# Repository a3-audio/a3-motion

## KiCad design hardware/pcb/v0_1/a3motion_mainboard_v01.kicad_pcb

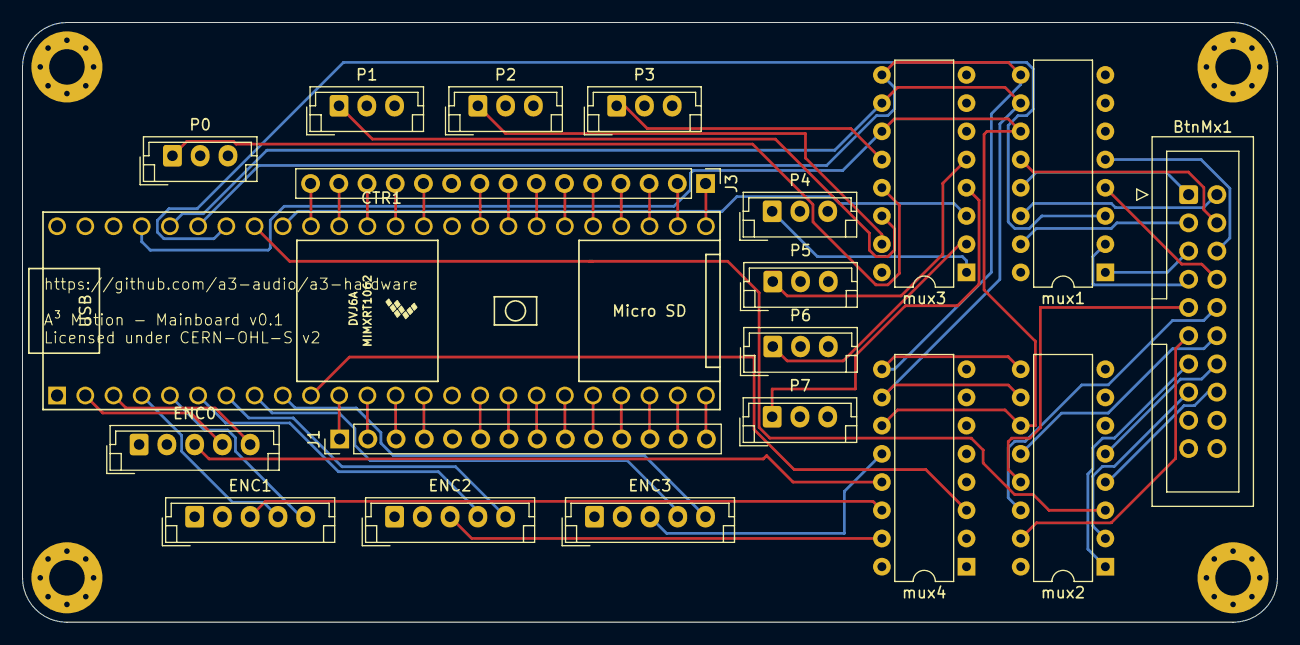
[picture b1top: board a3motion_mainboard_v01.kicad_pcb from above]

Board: 4 copper layers, 113.0 x 54.0 mm, 20 parts (0 on the bottom side), 72 nets.

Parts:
BtnMx1: Conn_02x09_Counter_Clockwise; IDC-Header_2x10_P2.54mm_Vertical
CTR1: Teensy4.1; Teensy41_my
ENC0, ENC1, ENC2, ENC3: Conn_01x05; JST_EH_B5B-EH-A_1x05_P2.50mm_Vertical
J1: Conn_01x14_Male; PinHeader_1x14_P2.54mm_Vertical
J3: Conn_01x15_Male; PinHeader_1x15_P2.54mm_Vertical
P0, P1, P2, P3, P4, P5, P6, P7: Conn_01x03; JST_EH_B3B-EH-A_1x03_P2.50mm_Vertical
mux1, mux2, mux3, mux4: 74HC4051; DIP-16_W7.62mm

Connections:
+3V3: BtnMx1.20, CTR1.15, CTR1.46, ENC0.2, ENC1.2, ENC2.2, ENC3.2, J1.5, P0.3, P1.3, P2.3, P3.3, P4.3, P5.3, P6.3, P7.3, mux1.16, mux2.16, mux3.16, mux4.16
GND: BtnMx1.19, CTR1.1, CTR1.34, CTR1.47, ENC0.1, ENC1.1, ENC2.1, ENC3.1, J3.10, P0.2, P1.2, P2.2, P3.2, P4.2, P5.2, P6.2, P7.2, mux1.6, mux1.7, mux1.8, mux2.6, mux2.7, mux2.8, mux3.6, mux3.7, mux3.8, mux4.6, mux4.7, mux4.8
unnamed: BtnMx1.1, mux1.13
unnamed: BtnMx1.2, mux1.14
unnamed: BtnMx1.3, mux1.15
unnamed: BtnMx1.4, mux1.12
unnamed: BtnMx1.5, mux1.1
unnamed: BtnMx1.6, mux1.5
unnamed: BtnMx1.7, mux1.2
unnamed: BtnMx1.8, mux1.4
unnamed: BtnMx1.9, mux2.13
unnamed: BtnMx1.10, mux2.14
unnamed: BtnMx1.11, mux2.15
unnamed: BtnMx1.12, mux2.12
unnamed: BtnMx1.13, mux2.1
unnamed: BtnMx1.14, mux2.5
unnamed: BtnMx1.15, mux2.2
unnamed: BtnMx1.16, mux2.4
unnamed: CTR1.11, J1.1
unnamed: CTR1.12, J1.2
unnamed: CTR1.13, J1.3
unnamed: CTR1.14, J1.4
unnamed: CTR1.16, J1.6
unnamed: CTR1.17, J1.7
unnamed: CTR1.18, J1.8
unnamed: CTR1.19, J1.9
unnamed: CTR1.20, J1.10
unnamed: CTR1.21, J1.11
unnamed: CTR1.22, J1.12
unnamed: CTR1.23, J1.13
unnamed: CTR1.24, J1.14
unnamed: CTR1.25, J3.1
unnamed: CTR1.26, J3.2
unnamed: CTR1.27, J3.3
unnamed: CTR1.28, J3.4
unnamed: CTR1.29, J3.5
unnamed: CTR1.30, J3.6
unnamed: CTR1.31, J3.7
unnamed: CTR1.32, J3.8
unnamed: CTR1.33, J3.9
unnamed: CTR1.35, J3.11
unnamed: CTR1.36, J3.12
unnamed: CTR1.37, J3.13
unnamed: CTR1.38, J3.14
unnamed: CTR1.39, J3.15
unnamed: ENC0.3, mux4.13
unnamed: ENC1.3, mux4.14
unnamed: ENC2.3, mux4.15
unnamed: ENC3.3, mux4.12
unnamed: P0.1, mux3.13
unnamed: P1.1, mux3.14
unnamed: P2.1, mux3.15
unnamed: P3.1, mux3.12
unnamed: P4.1, mux3.1
unnamed: P5.1, mux3.5
unnamed: P6.1, mux3.2
unnamed: P7.1, mux3.4
mux_btnMx1: CTR1.42, mux1.3
mux_btnMx2: CTR1.41, mux2.3
mux_btn_rEnc: CTR1.10, mux4.3
mux_porty: CTR1.40, mux3.3
rEnc0_CLK: CTR1.3, ENC0.5
rEnc0_DT: CTR1.2, ENC0.4
rEnc1_CLK: CTR1.5, ENC1.5
rEnc1_DT: CTR1.4, ENC1.4
rEnc2_CLK: CTR1.7, ENC2.5
rEnc2_DT: CTR1.6, ENC2.4
rEnc3_CLK: CTR1.9, ENC3.5
rEnc3_DT: CTR1.8, ENC3.4
s0: CTR1.45, mux1.11, mux2.11, mux3.11, mux4.11
s1: CTR1.44, mux1.10, mux2.10, mux3.10, mux4.10
s2: CTR1.43, mux1.9, mux2.9, mux3.9, mux4.9

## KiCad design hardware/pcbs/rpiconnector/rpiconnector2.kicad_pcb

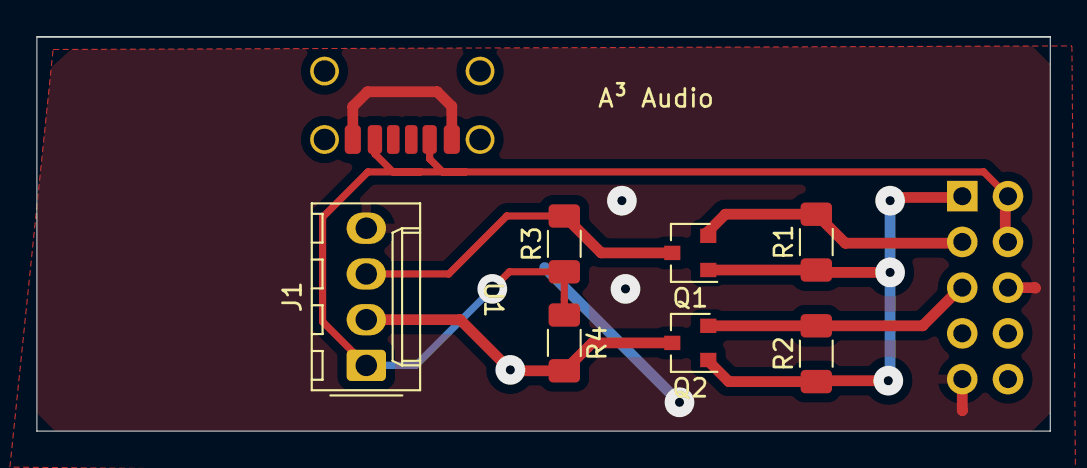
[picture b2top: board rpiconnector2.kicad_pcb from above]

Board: 2 copper layers, 56.3 x 21.9 mm, 9 parts (1 on the bottom side), 7 nets.

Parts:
J1: molex1x04; Molex_KK-254_AE-6410-04A_1x04_P2.54mm_Vertical
J2: Conn_02x05_Odd_Even; PinSocket_2x05_P2.54mm_Vertical
Q1, Q2: BSS138
R1, R2, R3, R4: 10k; R_1206_3216Metric_Pad1.30x1.75mm_HandSolder
U1: USB-C

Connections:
3v3: J2.1, Q1.1 (G), Q2.1 (G), R1.1, R2.1
5v: J1.1, J2.2, J2.4, R3.1, R4.1, U1.2 (VBUS), U1.5 (VBUS)
GND: J1.4, J2.6, J2.9, U1.1 (GND), U1.6 (GND)
SCL: J2.5, Q2.2 (S), R2.2
SCL_5V: J1.2, Q2.3 (D), R4.2
SDA: J2.3, Q1.2 (S), R1.2
SDA_5v: J1.3, Q1.3 (D), R3.2

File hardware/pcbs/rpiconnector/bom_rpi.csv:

"Reference","Value","Datasheet","Footprint","Qty","DNP"
"J1","molex1x04","~","Connector_Molex:Molex_KK-254_AE-6410-04A_1x04_P2.54mm_Vertical","1",""
"J2","Conn_02x10_Odd_Even","~","Connector_PinSocket_2.54mm:PinSocket_2x10_P2.54mm_Vertical","1",""
"Q1,Q2","BSS138","https://www.onsemi.com/pub/Collateral/BSS138-D.PDF","3dAudioFoot:BSS138","2",""
"R1,R2,R3,R4","10k","~","Resistor_SMD:R_1206_3216Metric_Pad1.30x1.75mm_HandSolder","4",""
"U1","USB-C","","3dAudioFoot:USB-C","1",""

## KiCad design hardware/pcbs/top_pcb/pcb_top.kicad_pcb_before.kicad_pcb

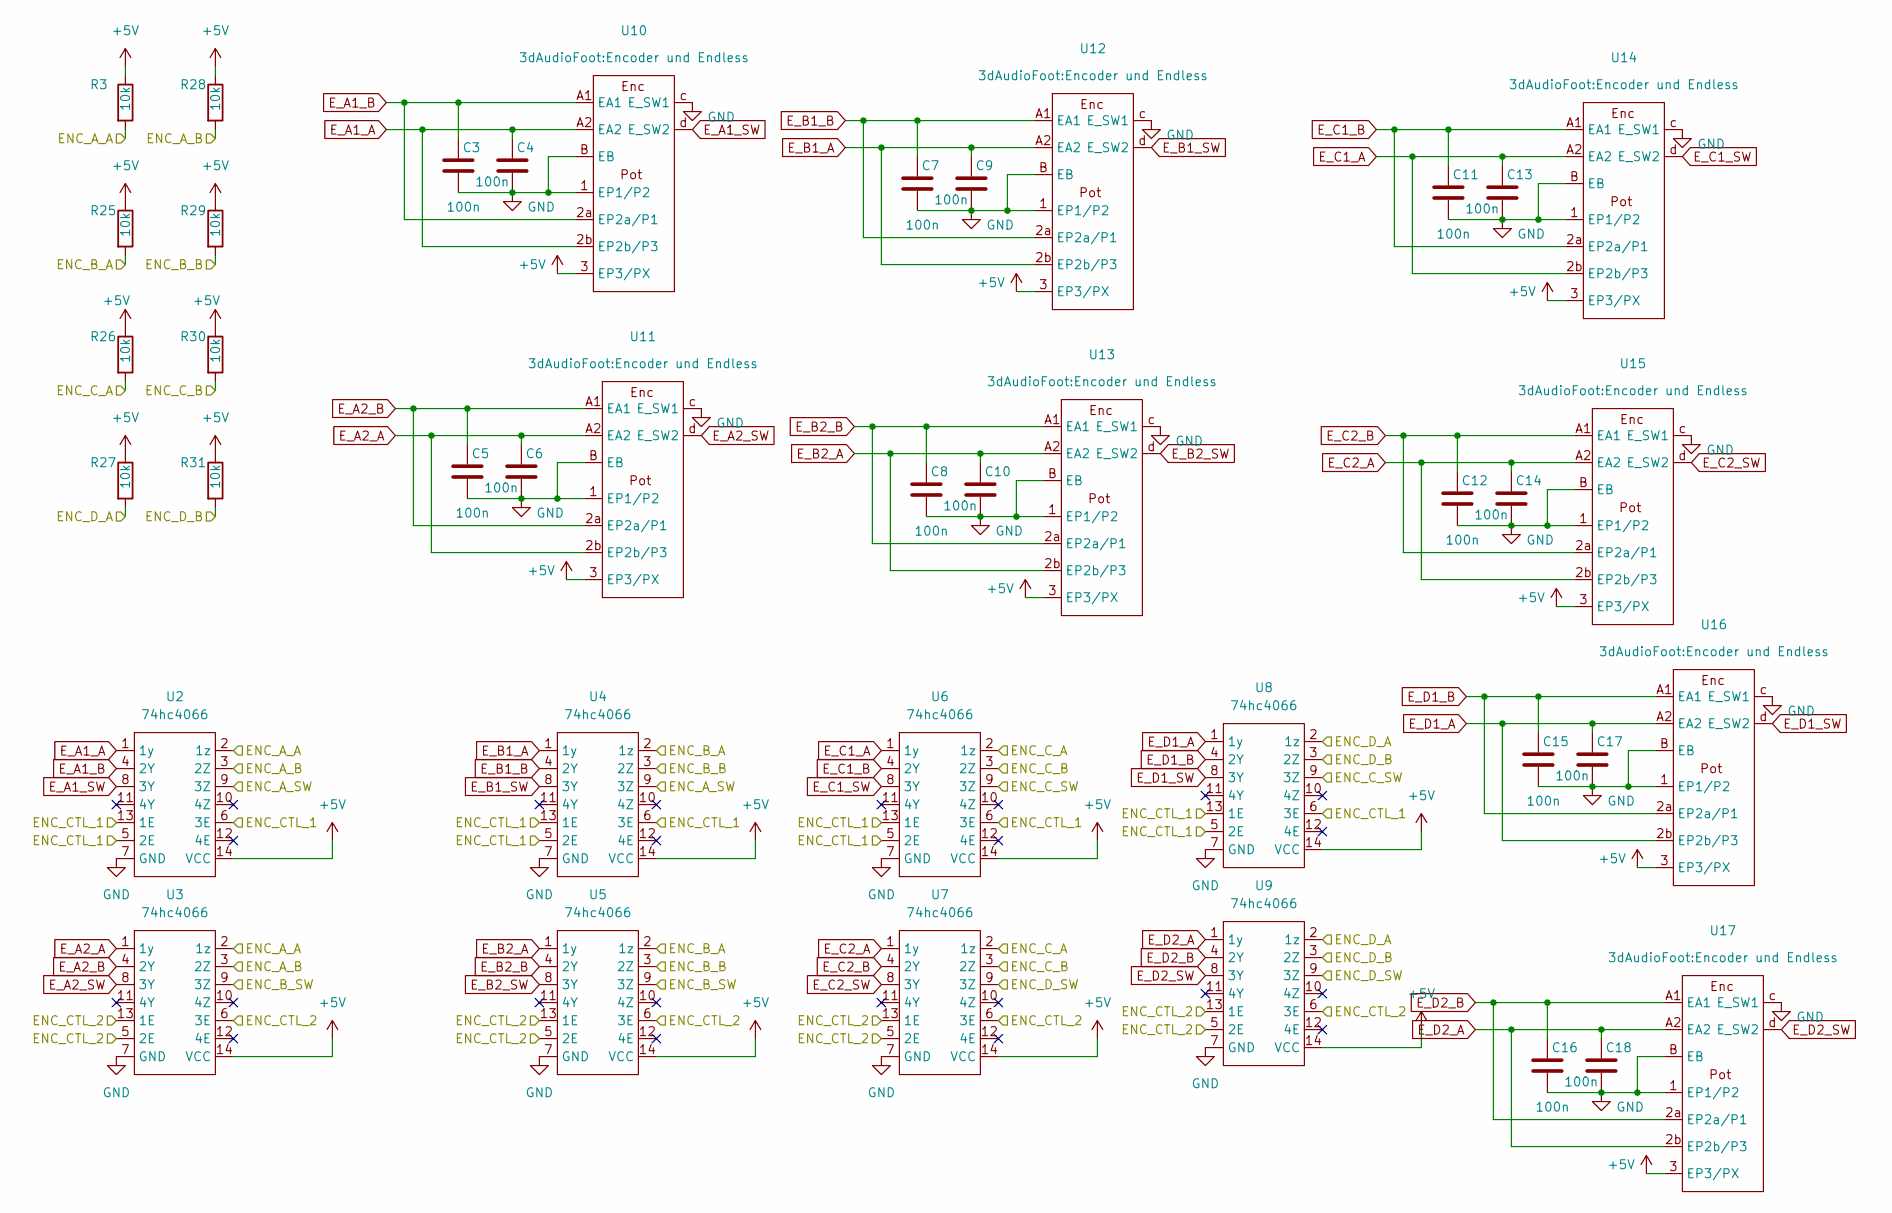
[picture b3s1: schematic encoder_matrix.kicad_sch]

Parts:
C3, C4, C5, C6, C7, C8, C9, C10, C11, C12, C13, C14, C15, C16, C17, C18: 100n; C_1206_3216Metric_Pad1.33x1.80mm_HandSolder
R3, R25, R26, R27, R28, R29, R30, R31: 10k; R_1206_3216Metric_Pad1.30x1.75mm_HandSolder
U2, U3, U4, U5, U6, U7, U8, U9: 74hc4066; SOIC-14_3.9x8.7mm_P1.27mm
U10, U11, U12, U13, U14, U15, U16, U17: Encoder und Endless

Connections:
+5V: R3.1, R25.1, R26.1, R27.1, R28.1, R29.1, R30.1, R31.1, U2.14 (VCC), U3.14 (VCC), U4.14 (VCC), U5.14 (VCC), U6.14 (VCC), U7.14 (VCC), U8.14 (VCC), U9.14 (VCC), U10.3 (EP3/PX), U11.3 (EP3/PX), U12.3 (EP3/PX), U13.3 (EP3/PX), U14.3 (EP3/PX), U15.3 (EP3/PX), U16.3 (EP3/PX), U17.3 (EP3/PX); also elsewhere on the board
/Untitled Sheet/ENC_A_A: R3.2, U2.2 (1z), U3.2 (1z); also elsewhere on the board
/Untitled Sheet/ENC_A_B: R28.2, U2.3 (2Z), U3.3 (2Z); also elsewhere on the board
/Untitled Sheet/ENC_A_SW: U2.9 (3Z), U4.9 (3Z); also elsewhere on the board
/Untitled Sheet/ENC_B_A: R25.2, U4.2 (1z), U5.2 (1z); also elsewhere on the board
/Untitled Sheet/ENC_B_B: R29.2, U4.3 (2Z), U5.3 (2Z); also elsewhere on the board
/Untitled Sheet/ENC_B_SW: U3.9 (3Z), U5.9 (3Z); also elsewhere on the board
/Untitled Sheet/ENC_CTL_1: U2.5 (2E), U2.6 (3E), U2.13 (1E), U4.5 (2E), U4.6 (3E), U4.13 (1E), U6.5 (2E), U6.6 (3E), U6.13 (1E), U8.5 (2E), U8.6 (3E), U8.13 (1E); also elsewhere on the board
/Untitled Sheet/ENC_CTL_2: U3.5 (2E), U3.6 (3E), U3.13 (1E), U5.5 (2E), U5.6 (3E), U5.13 (1E), U7.5 (2E), U7.6 (3E), U7.13 (1E), U9.5 (2E), U9.6 (3E), U9.13 (1E); also elsewhere on the board
/Untitled Sheet/ENC_C_A: R26.2, U6.2 (1z), U7.2 (1z); also elsewhere on the board
/Untitled Sheet/ENC_C_B: R30.2, U6.3 (2Z), U7.3 (2Z); also elsewhere on the board
/Untitled Sheet/ENC_C_SW: U6.9 (3Z), U8.9 (3Z); also elsewhere on the board
/Untitled Sheet/ENC_D_A: R27.2, U8.2 (1z), U9.2 (1z); also elsewhere on the board
/Untitled Sheet/ENC_D_B: R31.2, U8.3 (2Z), U9.3 (2Z); also elsewhere on the board
/Untitled Sheet/ENC_D_SW: U7.9 (3Z), U9.9 (3Z); also elsewhere on the board
E_A1_A: C4.1, U2.1 (1y), U10.2b (EP2b/P3), U10.A2 (EA2)
E_A1_B: C3.1, U2.4 (2Y), U10.2a (EP2a/P1), U10.A1 (EA1)
E_A1_SW: U2.8 (3Y), U10.d (E_SW2)
E_A2_A: C6.1, U3.1 (1y), U11.2b (EP2b/P3), U11.A2 (EA2)
E_A2_B: C5.1, U3.4 (2Y), U11.2a (EP2a/P1), U11.A1 (EA1)
E_A2_SW: U3.8 (3Y), U11.d (E_SW2)
E_B1_A: C9.1, U4.1 (1y), U12.2b (EP2b/P3), U12.A2 (EA2)
E_B1_B: C7.1, U4.4 (2Y), U12.2a (EP2a/P1), U12.A1 (EA1)
E_B1_SW: U4.8 (3Y), U12.d (E_SW2)
E_B2_A: C10.1, U5.1 (1y), U13.2b (EP2b/P3), U13.A2 (EA2)
E_B2_B: C8.1, U5.4 (2Y), U13.2a (EP2a/P1), U13.A1 (EA1)
E_B2_SW: U5.8 (3Y), U13.d (E_SW2)
E_C1_A: C13.1, U6.1 (1y), U14.2b (EP2b/P3), U14.A2 (EA2)
E_C1_B: C11.1, U6.4 (2Y), U14.2a (EP2a/P1), U14.A1 (EA1)
E_C1_SW: U6.8 (3Y), U14.d (E_SW2)
E_C2_A: C14.1, U7.1 (1y), U15.2b (EP2b/P3), U15.A2 (EA2)
E_C2_B: C12.1, U7.4 (2Y), U15.2a (EP2a/P1), U15.A1 (EA1)
E_C2_SW: U7.8 (3Y), U15.d (E_SW2)
E_D1_A: C17.1, U8.1 (1y), U16.2b (EP2b/P3), U16.A2 (EA2)
E_D1_B: C15.1, U8.4 (2Y), U16.2a (EP2a/P1), U16.A1 (EA1)
E_D1_SW: U8.8 (3Y), U16.d (E_SW2)
E_D2_A: C18.1, U9.1 (1y), U17.2b (EP2b/P3), U17.A2 (EA2)
E_D2_B: C16.1, U9.4 (2Y), U17.2a (EP2a/P1), U17.A1 (EA1)
E_D2_SW: U9.8 (3Y), U17.d (E_SW2)
GND: C3.2, C4.2, C5.2, C6.2, C7.2, C8.2, C9.2, C10.2, C11.2, C12.2, C13.2, C14.2, C15.2, C16.2, C17.2, C18.2, U2.7 (GND), U3.7 (GND), U4.7 (GND), U5.7 (GND), U6.7 (GND), U7.7 (GND), U8.7 (GND), U9.7 (GND), U10.1 (EP1/P2), U10.B (EB), U10.c (E_SW1), U11.1 (EP1/P2), U11.B (EB), U11.c (E_SW1), U12.1 (EP1/P2), U12.B (EB), U12.c (E_SW1), U13.1 (EP1/P2), U13.B (EB), U13.c (E_SW1), U14.1 (EP1/P2), U14.B (EB), U14.c (E_SW1), U15.1 (EP1/P2), U15.B (EB), U15.c (E_SW1), U16.1 (EP1/P2), U16.B (EB), U16.c (E_SW1), U17.1 (EP1/P2), U17.B (EB), U17.c (E_SW1); also elsewhere on the board

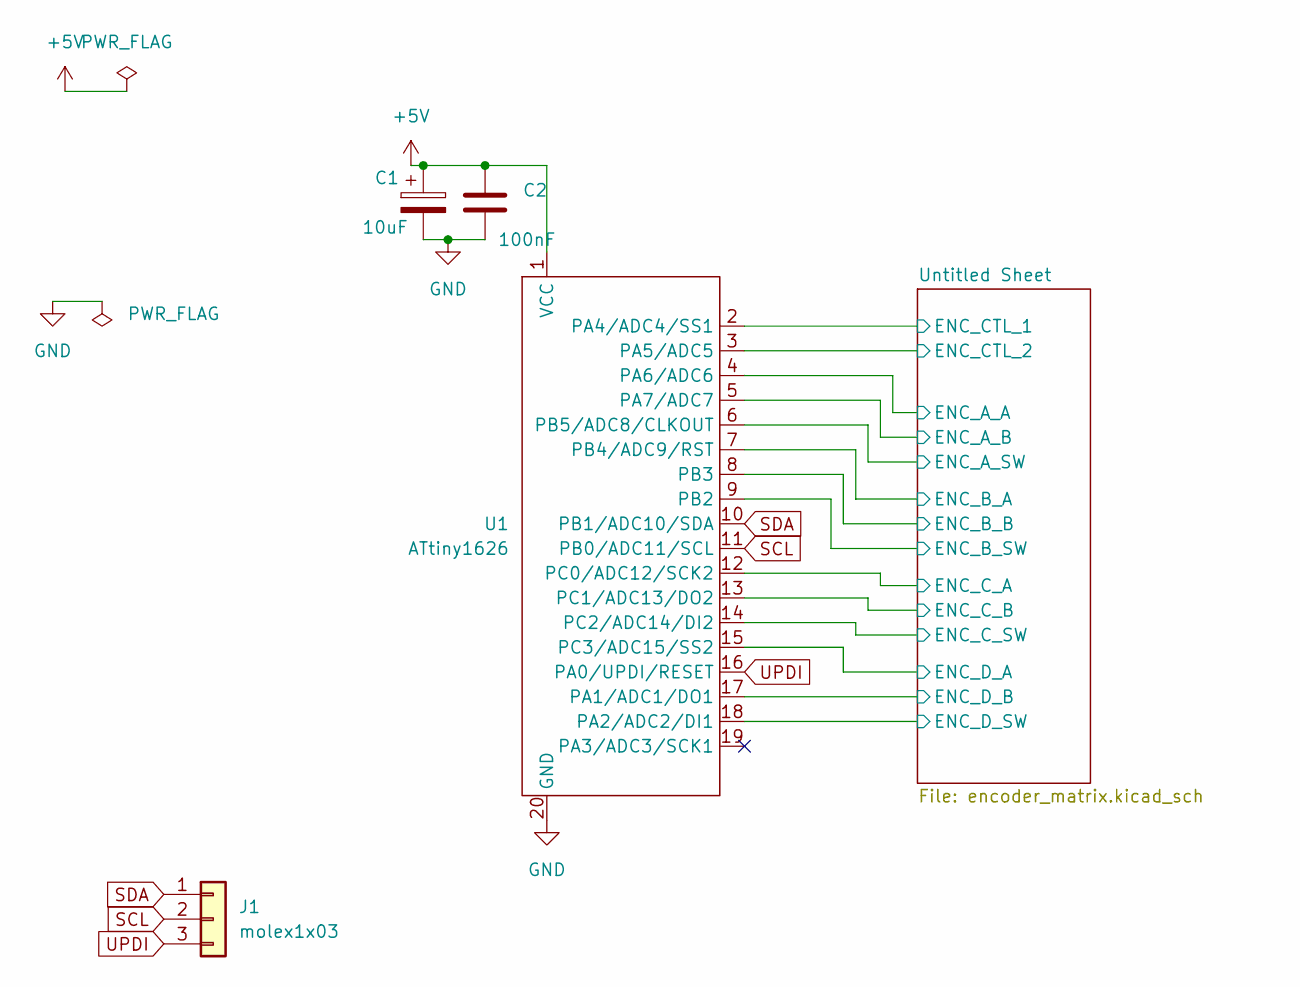
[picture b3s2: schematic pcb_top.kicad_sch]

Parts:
C1: 10uF; CP_Radial_D4.0mm_P1.50mm
C2: 100nF; C_1206_3216Metric_Pad1.33x1.80mm_HandSolder
J1: molex1x03; Molex_KK-254_AE-6410-03A_1x03_P2.54mm_Vertical
U1: ATtiny1626; attiny1626

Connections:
+5V: C1.1, C2.1, U1.1 (VCC); also elsewhere on the board
/Untitled Sheet/ENC_A_A: U1.4 (PA6/ADC6); also elsewhere on the board
/Untitled Sheet/ENC_A_B: U1.5 (PA7/ADC7); also elsewhere on the board
/Untitled Sheet/ENC_A_SW: U1.6 (PB5/ADC8/CLKOUT); also elsewhere on the board
/Untitled Sheet/ENC_B_A: U1.7 (PB4/ADC9/RST); also elsewhere on the board
/Untitled Sheet/ENC_B_B: U1.8 (PB3); also elsewhere on the board
/Untitled Sheet/ENC_B_SW: U1.9 (PB2); also elsewhere on the board
/Untitled Sheet/ENC_CTL_1: U1.2 (PA4/ADC4/SS1); also elsewhere on the board
/Untitled Sheet/ENC_CTL_2: U1.3 (PA5/ADC5); also elsewhere on the board
/Untitled Sheet/ENC_C_A: U1.12 (PC0/ADC12/SCK2); also elsewhere on the board
/Untitled Sheet/ENC_C_B: U1.13 (PC1/ADC13/DO2); also elsewhere on the board
/Untitled Sheet/ENC_C_SW: U1.14 (PC2/ADC14/DI2); also elsewhere on the board
/Untitled Sheet/ENC_D_A: U1.15 (PC3/ADC15/SS2); also elsewhere on the board
/Untitled Sheet/ENC_D_B: U1.17 (PA1/ADC1/DO1); also elsewhere on the board
/Untitled Sheet/ENC_D_SW: U1.18 (PA2/ADC2/DI1); also elsewhere on the board
GND: C1.2, C2.2, U1.20 (GND); also elsewhere on the board
SCL: J1.2, U1.11 (PB0/ADC11/SCL)
SDA: J1.1, U1.10 (PB1/ADC10/SDA)
UPDI: J1.3, U1.16 (PA0/UPDI/RESET)

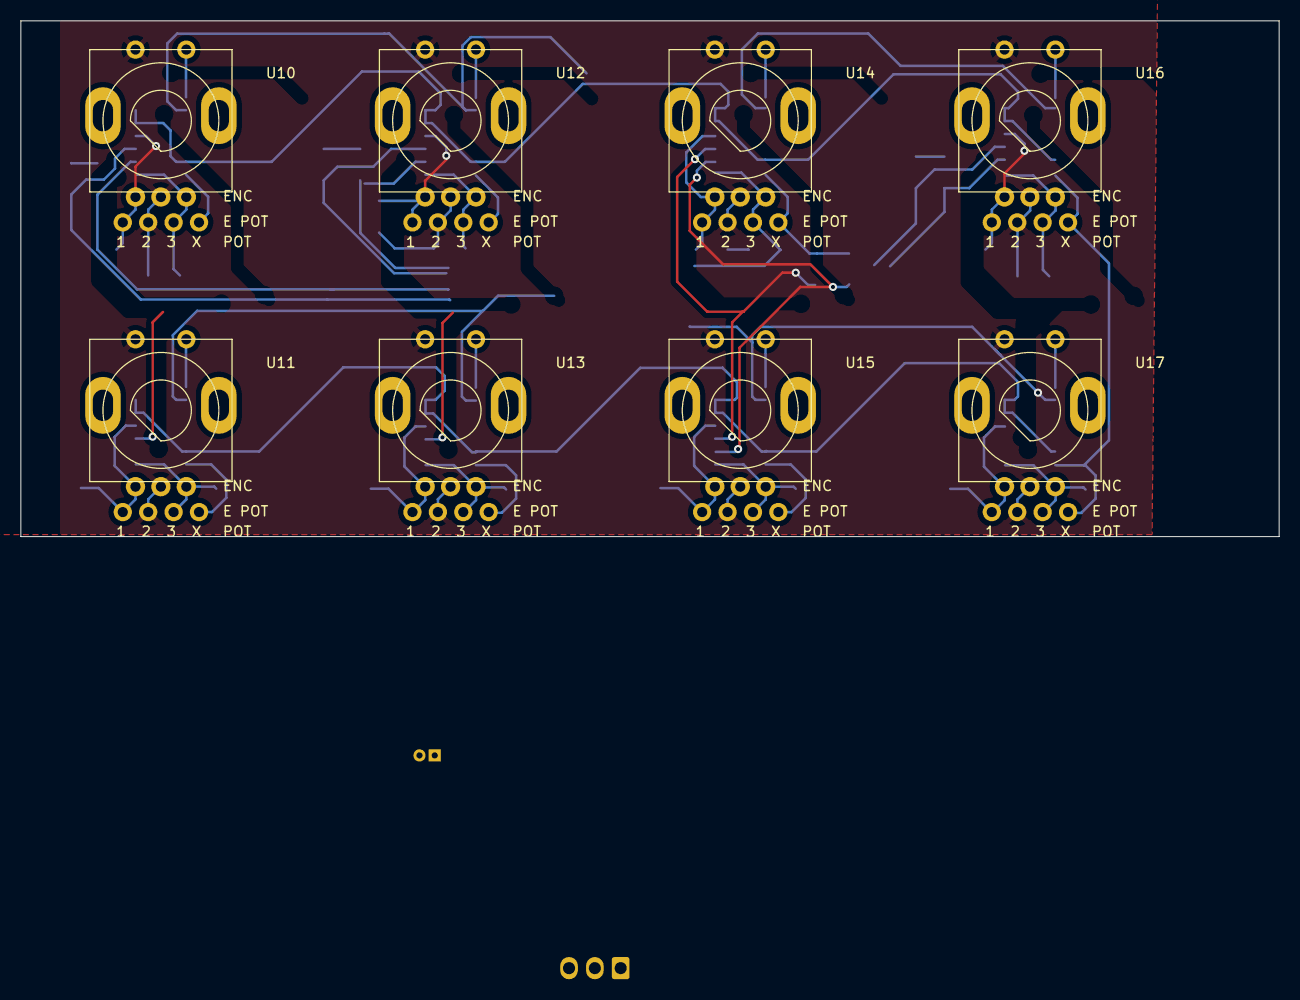
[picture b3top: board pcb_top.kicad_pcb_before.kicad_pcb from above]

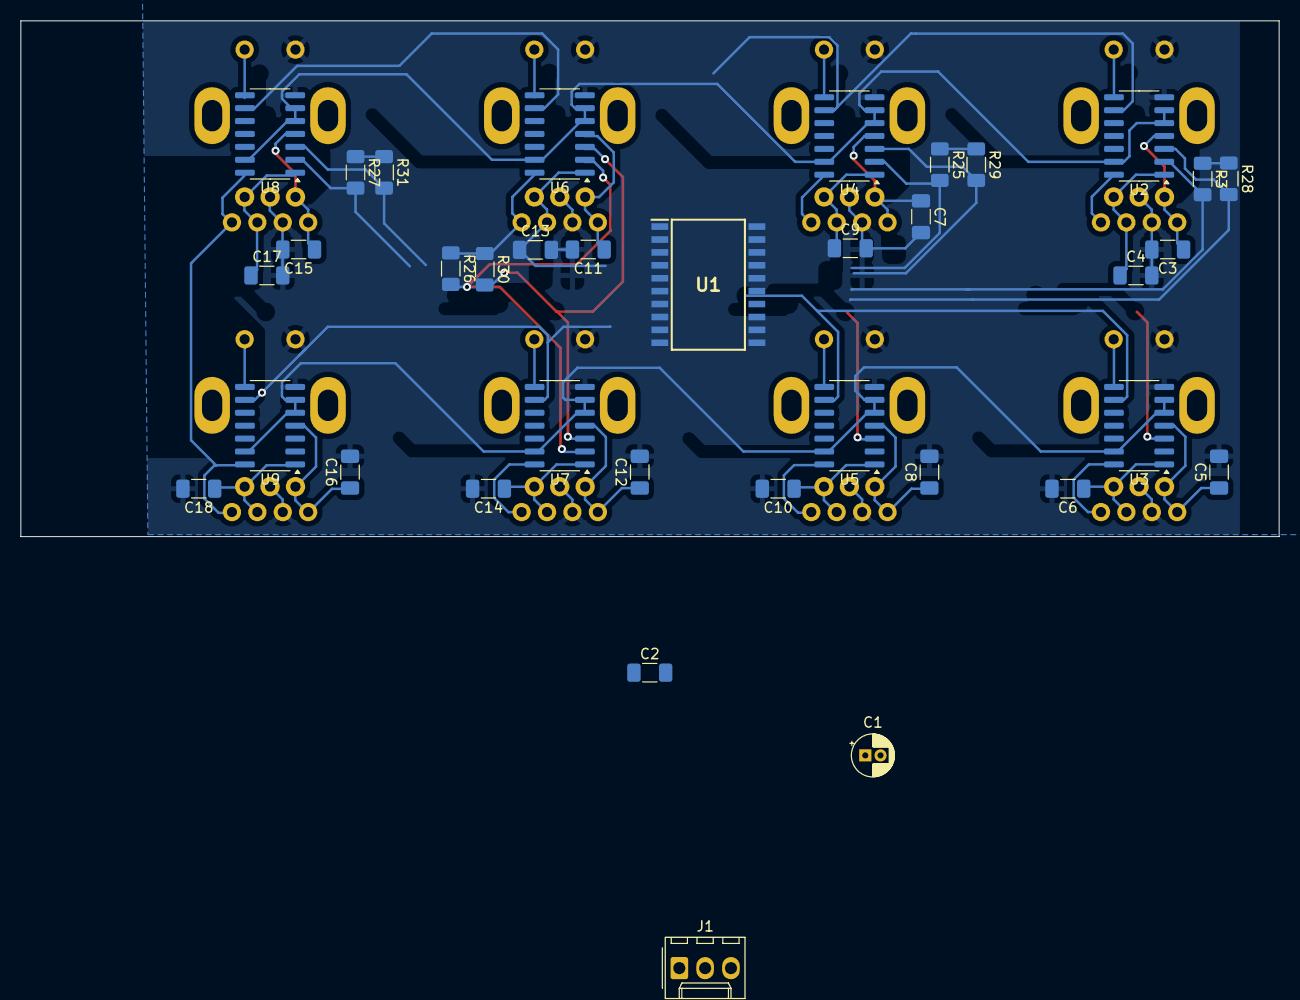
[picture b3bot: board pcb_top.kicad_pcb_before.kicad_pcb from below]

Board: 2 copper layers, 123.8 x 50.7 mm, 44 parts (36 on the bottom side), 43 nets.

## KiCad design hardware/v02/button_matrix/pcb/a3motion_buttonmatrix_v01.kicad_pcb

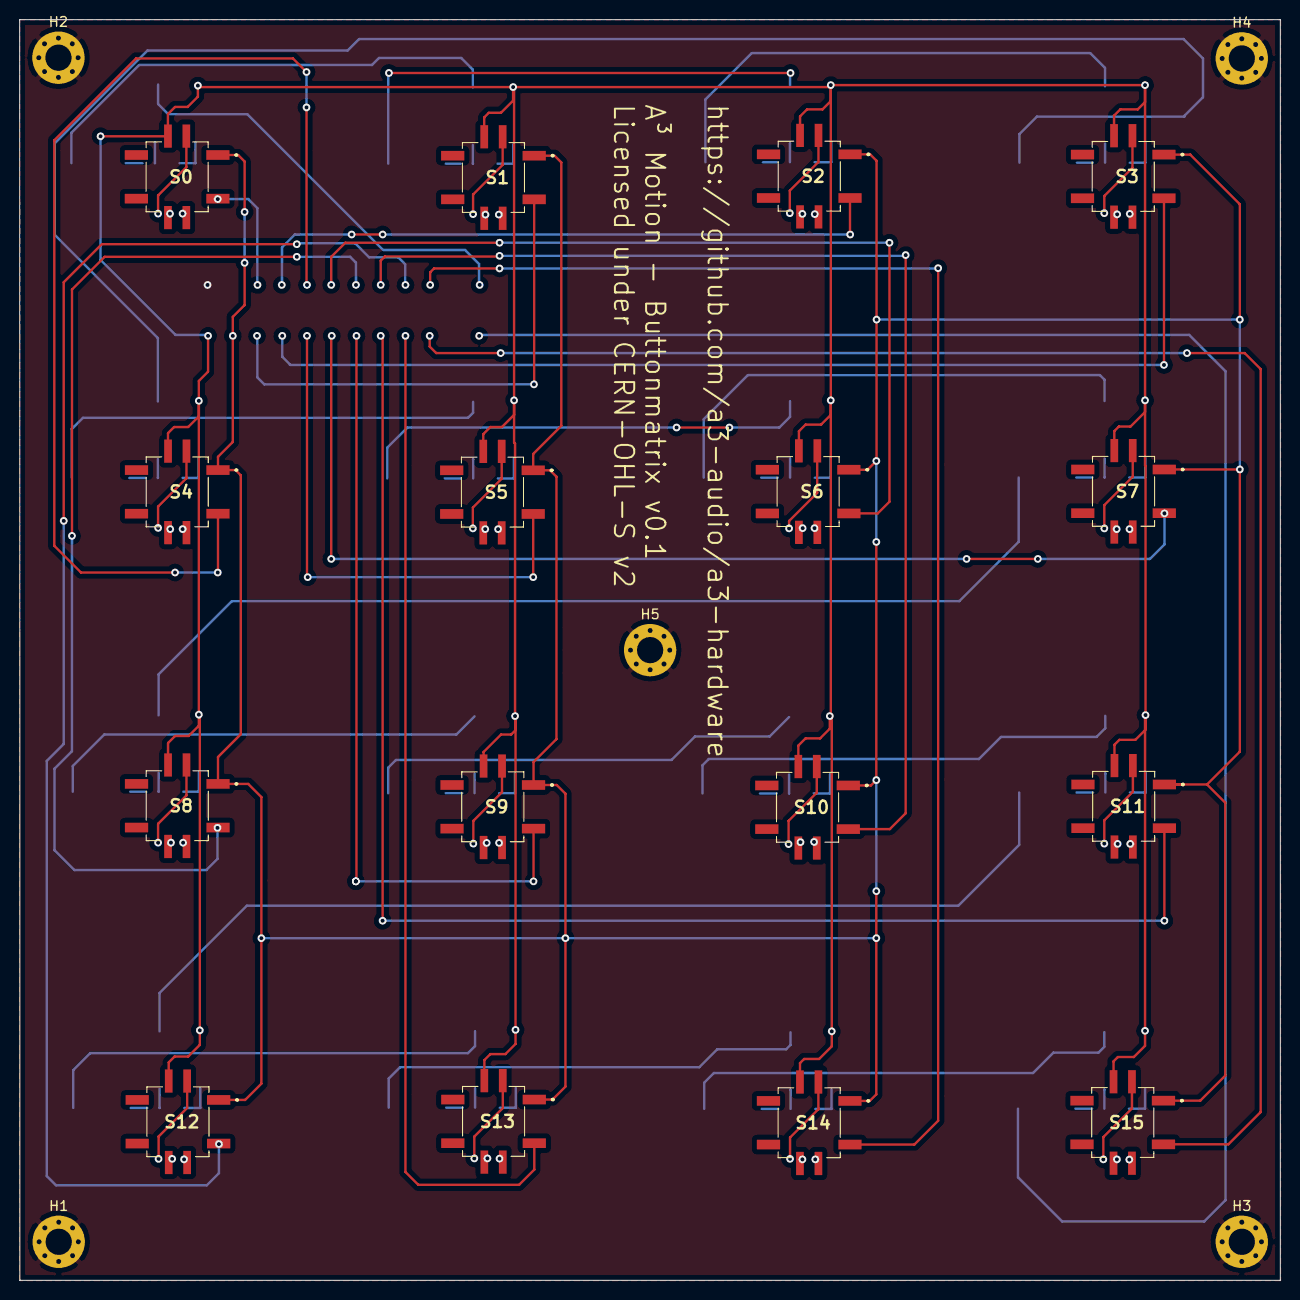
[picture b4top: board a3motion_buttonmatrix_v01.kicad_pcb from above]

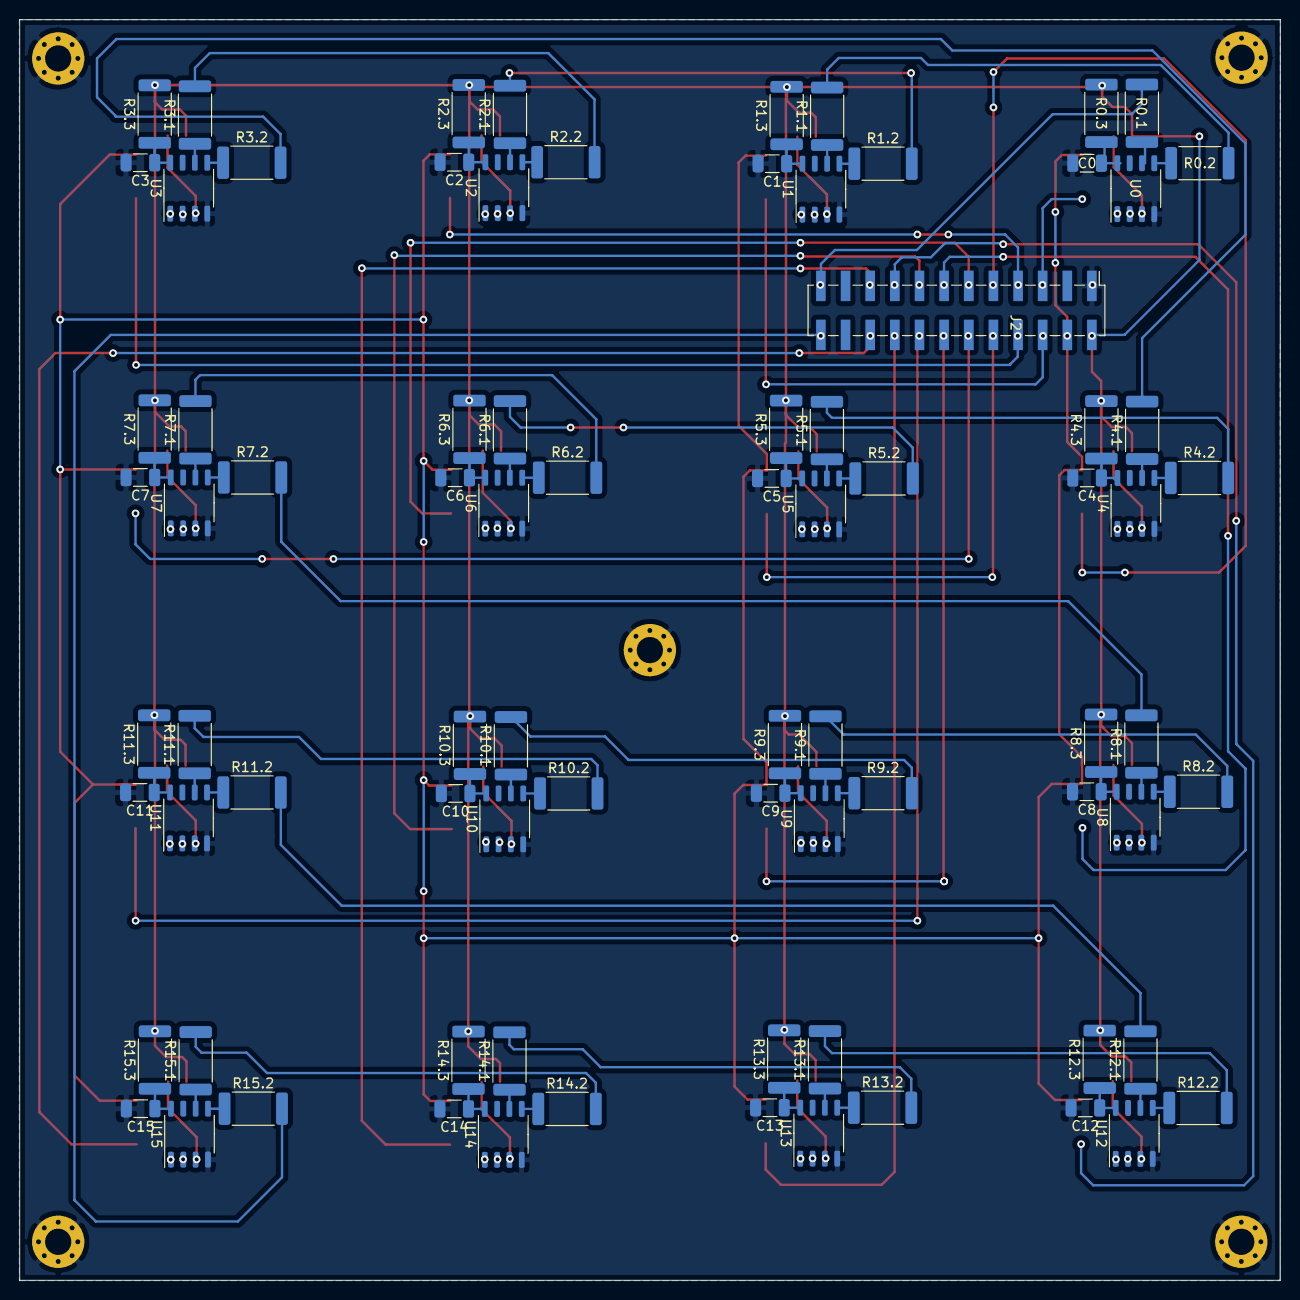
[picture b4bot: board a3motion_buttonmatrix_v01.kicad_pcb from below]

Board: 2 copper layers, 130.0 x 130.0 mm, 102 parts (81 on the bottom side), 132 nets.

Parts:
C0, C1, C2, C3, C4, C5, C6, C7, C8, C9, C10, C11, C12, C13, C14, C15: 104; C_1206_3216Metric
H1, H2, H3, H4, H5: MountingHole_Pad; MountingHole_2.7mm_Pad_Via
J2: Conn_02x12_Odd_Even; PinHeader_2x12_P2.54mm_Vertical_SMD
R0.1, R0.2, R1.1, R1.2, R2.1, R2.2, R3.1, R3.2, R4.1, R4.2, R5.1, R5.2, R6.1, R6.2, R7.1, R7.2, R8.1, R8.2, R9.1, R9.2, R10.1, R10.2, R11.1, R11.2, R12.1, R12.2, R13.1, R13.2, R14.1, R14.2, R15.1, R15.2: 33; R_2512_6332Metric
R0.3, R1.3, R2.3, R3.3, R4.3, R5.3, R6.3, R7.3, R8.3, R9.3, R10.3, R11.3, R12.3, R13.3, R14.3, R15.3: 100; R_2512_6332Metric
S0, S1, S2, S3, S4, S5, S6, S7, S8, S9, S10, S11, S12, S13, S14, S15: 228CMVARGBFR
U0, U1, U2, U3, U4, U5, U6, U7, U8, U9, U10, U11, U12, U13, U14, U15: WS2811; SOP-8_3.9x4.9mm_P1.27mm

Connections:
+3V3: J2.4, S0.1, S1.1, S2.1, S3.1, S4.1, S5.1, S6.1, S7.1, S8.1, S9.1, S10.1, S11.1, S12.1, S13.1, S14.1, S15.1
+5V: J2.2, R0.3.2, R1.3.2, R2.3.2, R3.3.2, R4.3.2, R5.3.2, R6.3.2, R7.3.2, R8.3.2, R9.3.2, R10.3.2, R11.3.2, R12.3.2, R13.3.2, R14.3.2, R15.3.2, S0.L3, S1.L3, S2.L3, S3.L3, S4.L3, S5.L3, S6.L3, S7.L3, S8.L3, S9.L3, S10.L3, S11.L3, S12.L3, S13.L3, S14.L3, S15.L3
GND: C0.2, C1.2, C2.2, C3.2, C4.2, C5.2, C6.2, C7.2, C8.2, C9.2, C10.2, C11.2, C12.2, C13.2, C14.2, C15.2, H1.1, H2.1, H3.1, H4.1, H5.1, J2.1, U0.4, U1.4, U2.4, U3.4, U4.4, U5.4, U6.4, U7.4, U8.4, U9.4, U10.4, U11.4, U12.4, U13.4, U14.4, U15.4
LED_DAT_IN: J2.23, R0.1.2
LED_DAT_OUT: J2.24, R15.2.2
unnamed: C0.1, R0.3.1, U0.8
unnamed: C1.1, R1.3.1, U1.8
unnamed: C2.1, R2.3.1, U2.8
unnamed: C3.1, R3.3.1, U3.8
unnamed: C4.1, R4.3.1, U4.8
unnamed: C5.1, R5.3.1, U5.8
unnamed: C6.1, R6.3.1, U6.8
unnamed: C7.1, R7.3.1, U7.8
unnamed: C8.1, R8.3.1, U8.8
unnamed: C9.1, R9.3.1, U9.8
unnamed: C10.1, R10.3.1, U10.8
unnamed: C11.1, R11.3.1, U11.8
unnamed: C12.1, R12.3.1, U12.8
unnamed: C13.1, R13.3.1, U13.8
unnamed: C14.1, R14.3.1, U14.8
unnamed: C15.1, R15.3.1, U15.8
unnamed: R0.1.1, U0.6
unnamed: R0.2.1, U0.5
unnamed: R0.2.2, R1.1.2
unnamed: R1.1.1, U1.6
unnamed: R1.2.1, U1.5
unnamed: R1.2.2, R2.1.2
unnamed: R2.1.1, U2.6
unnamed: R2.2.1, U2.5
unnamed: R2.2.2, R3.1.2
unnamed: R3.1.1, U3.6
unnamed: R3.2.1, U3.5
unnamed: R3.2.2, R4.1.2
unnamed: R4.1.1, U4.6
unnamed: R4.2.1, U4.5
unnamed: R4.2.2, R5.1.2
unnamed: R5.1.1, U5.6
unnamed: R5.2.1, U5.5
unnamed: R5.2.2, R6.1.2
unnamed: R6.1.1, U6.6
unnamed: R6.2.1, U6.5
unnamed: R6.2.2, R7.1.2
unnamed: R7.1.1, U7.6
unnamed: R7.2.1, U7.5
unnamed: R7.2.2, R8.1.2
unnamed: R8.1.1, U8.6
unnamed: R8.2.1, U8.5
unnamed: R8.2.2, R9.1.2
unnamed: R9.1.1, U9.6
unnamed: R9.2.1, U9.5
unnamed: R10.1.1, U10.6
unnamed: R9.2.2, R10.1.2
unnamed: R10.2.1, U10.5
unnamed: R10.2.2, R11.1.2
unnamed: R11.1.1, U11.6
unnamed: R11.2.1, U11.5
unnamed: R11.2.2, R12.1.2
unnamed: R12.1.1, U12.6
unnamed: R12.2.1, U12.5
unnamed: R12.2.2, R13.1.2
unnamed: R13.1.1, U13.6
unnamed: R13.2.1, U13.5
unnamed: R13.2.2, R14.1.2
unnamed: R14.1.1, U14.6
unnamed: R14.2.1, U14.5
unnamed: R14.2.2, R15.1.2
unnamed: R15.1.1, U15.6
unnamed: R15.2.1, U15.5
unnamed: S0.L1, U0.3
unnamed: S0.L2, U0.1
unnamed: S0.L4, U0.2
unnamed: S1.L1, U1.3
unnamed: S1.L2, U1.1
unnamed: S1.L4, U1.2
unnamed: S2.L1, U2.3
unnamed: S2.L2, U2.1
unnamed: S2.L4, U2.2
unnamed: S3.L1, U3.3
unnamed: S3.L2, U3.1
unnamed: S3.L4, U3.2
unnamed: S4.L1, U4.3
unnamed: S4.L2, U4.1
unnamed: S4.L4, U4.2
unnamed: S5.L1, U5.3
unnamed: S5.L2, U5.1
unnamed: S5.L4, U5.2
unnamed: S6.L1, U6.3
unnamed: S6.L2, U6.1
unnamed: S6.L4, U6.2
unnamed: S7.L1, U7.3
unnamed: S7.L2, U7.1
unnamed: S7.L4, U7.2
unnamed: S8.L1, U8.3
unnamed: S8.L2, U8.1
unnamed: S8.L4, U8.2
unnamed: S9.L1, U9.3
unnamed: S9.L2, U9.1
unnamed: S9.L4, U9.2
unnamed: S10.L1, U10.3
unnamed: S10.L2, U10.1
unnamed: S10.L4, U10.2
unnamed: S11.L1, U11.3
unnamed: S11.L2, U11.1
unnamed: S11.L4, U11.2
unnamed: S12.L1, U12.3
unnamed: S12.L2, U12.1
unnamed: S12.L4, U12.2
unnamed: S13.L1, U13.3
unnamed: S13.L2, U13.1
unnamed: S13.L4, U13.2
unnamed: S14.L1, U14.3
unnamed: S14.L2, U14.1
unnamed: S14.L4, U14.2
unnamed: S15.L1, U15.3
unnamed: S15.L2, U15.1
unnamed: S15.L4, U15.2
btn00: J2.5, S0.3
btn01: J2.6, S1.3
btn02: J2.7, S2.3
btn03: J2.8, S3.3
btn04: J2.9, S4.3
btn05: J2.10, S5.3
btn06: J2.11, S6.3
btn07: J2.12, S7.3
btn08: J2.13, S8.3
btn09: J2.14, S9.3
btn10: J2.15, S10.3
btn11: J2.16, S11.3
btn12: J2.17, S12.3
btn13: J2.18, S13.3
btn14: J2.19, S14.3
btn15: J2.20, S15.3

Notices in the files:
hardware/pcb/v0_1/a3motion_mainboard_v01.kicad_pcb:
Licensed under CERN-OHL-S v2
hardware/v03.1/moc-pcb/controller_motion_pcb.kicad_sch:
Licensed under CERN-OHL-S v2 or later
